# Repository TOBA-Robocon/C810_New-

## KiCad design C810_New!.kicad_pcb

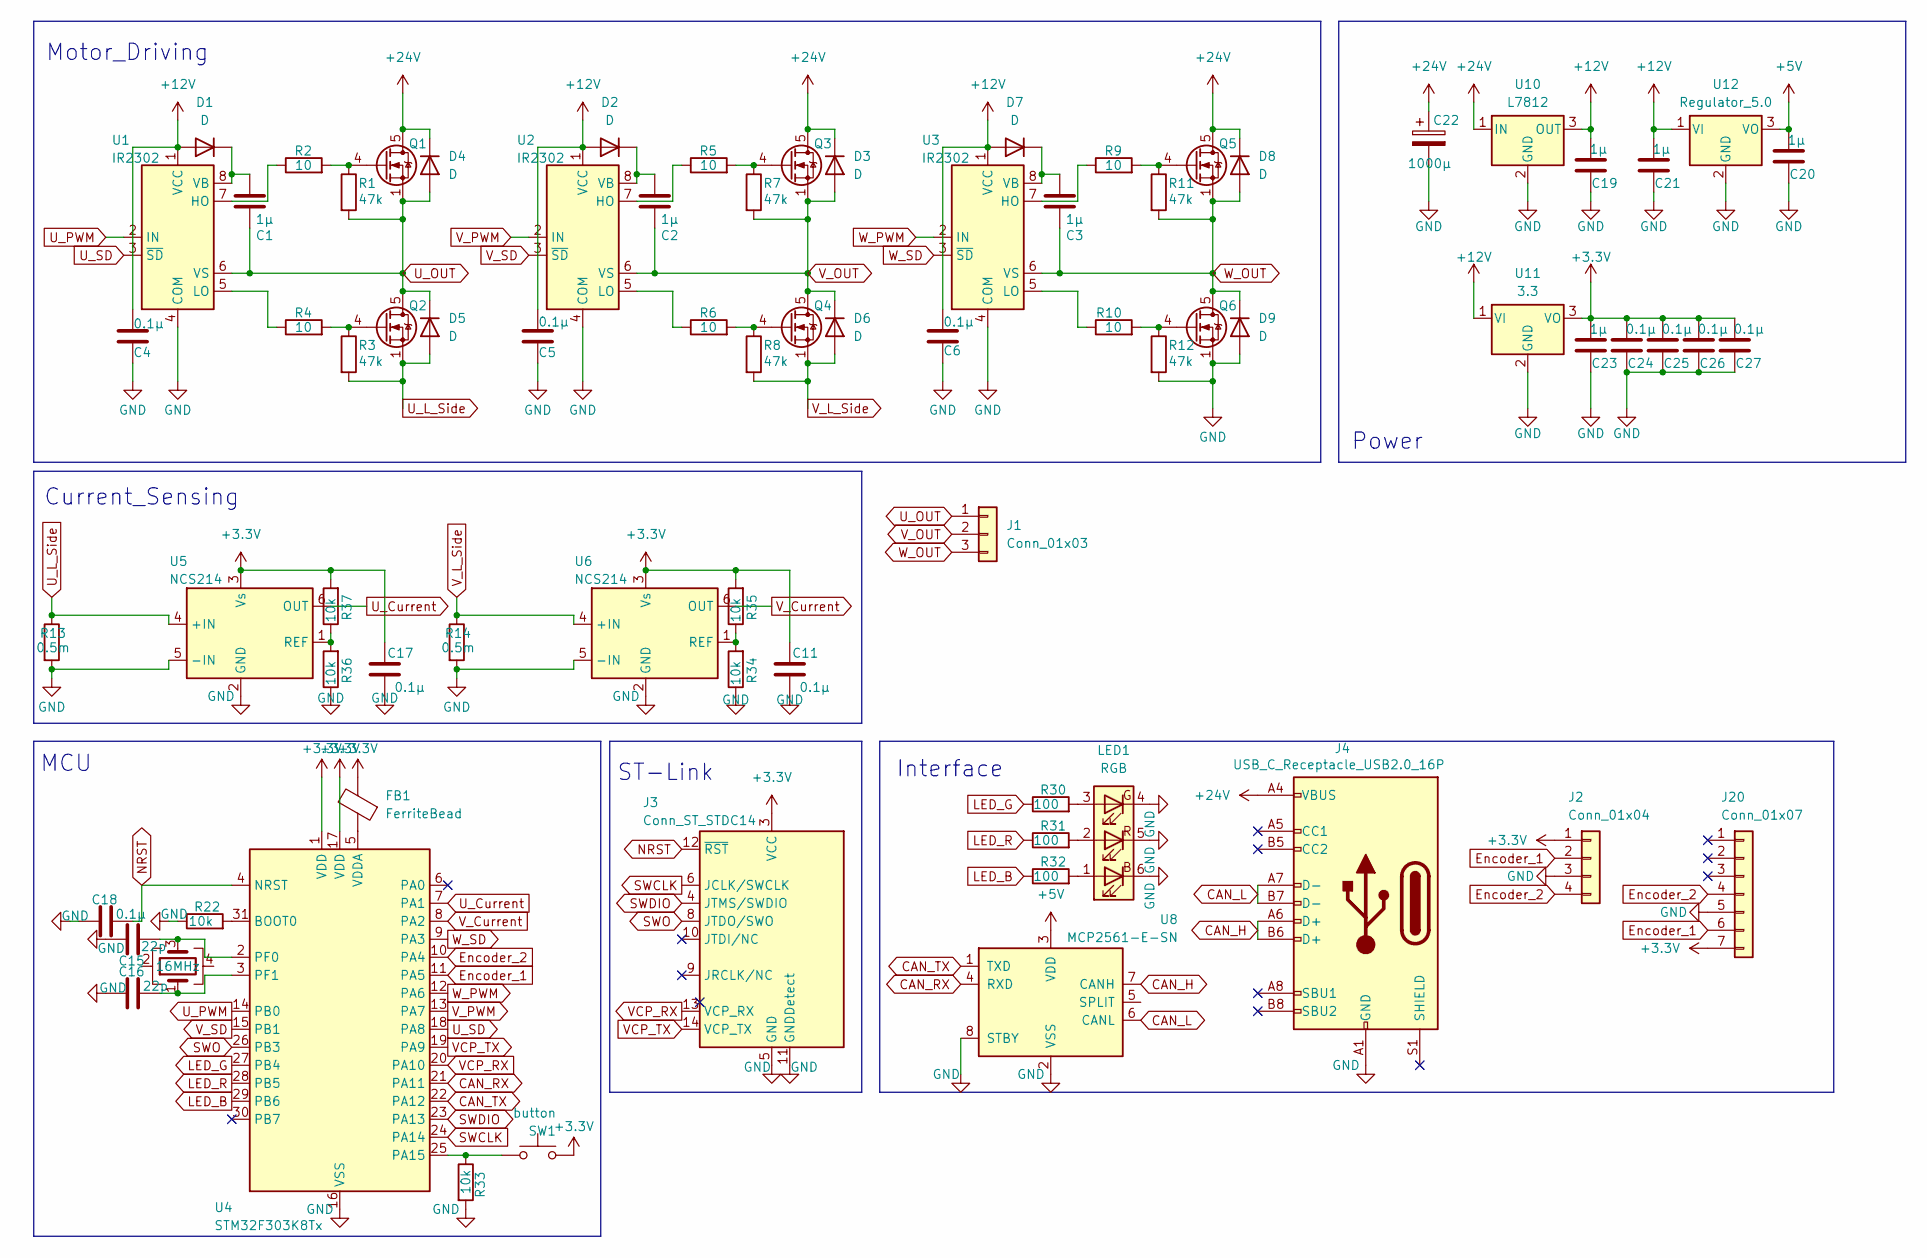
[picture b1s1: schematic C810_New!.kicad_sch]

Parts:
C1, C2, C3, C19, C20, C21, C23: 1μ; C_0603_1608Metric
C4, C5, C6, C11, C17, C18, C24, C25, C26, C27: 0.1μ; C_0603_1608Metric
C15, C16: 22p; C_0603_1608Metric
C22: 1000μ; CP_Elec_6.3x7.7
D1, D2, D3, D4, D5, D6, D7, D8, D9: D; D_SOD-123F
FB1: FerriteBead; L_0805_2012Metric_Pad1.05x1.20mm_HandSolder
J1: Conn_01x03; MR30
J2: Conn_01x04; JST_GH_SM04B-GHS-TB_1x04-1MP_P1.25mm_Horizontal
J3: Conn_ST_STDC14; PinHeader_2x07_P1.27mm_Vertical
J4: USB_C_Receptacle_USB2.0_16P; USB_C_Receptacle_GCT_USB4085
J20: Conn_01x07; JST_GH_SM07B-GHS-TB_1x07-1MP_P1.25mm_Horizontal
LED1: RGB; LED_ROHM_SMLVN6
Q1, Q2, Q3, Q4, Q5, Q6: BSC159N10LSFG; TDSON-8-1
R1, R3, R7, R8, R11, R12: 47k; R_0603_1608Metric
R2, R4, R5, R6, R9, R10: 10; R_0603_1608Metric
R13, R14: 0.5m; R_2512_6332Metric
R22, R33, R34, R35, R36, R37: 10k; R_0603_1608Metric
R30, R31, R32: 100; R_0603_1608Metric
SW1: button; SW_Push_1P1T_NO_Vertical_Wuerth_434133025816
U1, U2, U3: IR2302; SOIC-8_3.9x4.9mm_P1.27mm
U4: STM32F303K8Tx; LQFP-32_7x7mm_P0.8mm
U5, U6: NCS214; SOT-363_SC-70-6_Handsoldering
U8: MCP2561-E-SN; SOIC-8_3.9x4.9mm_P1.27mm
U10: L7812; TO-252-2
U11: 3.3; TO-252-2
U12: Regulator_5.0; TO-252-2
Y2: 16MHz; Crystal_SMD_3225-4Pin_3.2x2.5mm

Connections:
+3.3V: C11.1, C17.1, C23.1, C24.1, C25.1, C26.1, C27.1, FB1.2, J2.1, J3.3 (VCC), J20.7, R35.2, R37.2, SW1.2, U4.1 (VDD), U4.17 (VDD), U5.3 (Vs), U6.3 (Vs), U11.3 (VO)
+5V: C20.1, U8.3 (VDD), U12.3 (VO)
+12V: C4.1, C5.1, C6.1, C19.1, C21.1, D1.2 (A), D2.2 (A), D7.2 (A), U1.1 (VCC), U2.1 (VCC), U3.1 (VCC), U10.3 (OUT), U11.1 (VI), U12.1 (VI)
+24V: C22.1, D3.1 (K), D4.1 (K), D8.1 (K), J4.A4 (VBUS), J4.A9 (VBUS), J4.B4 (VBUS), J4.B9 (VBUS), Q1.5 (D), Q3.5 (D), Q5.5 (D), U10.1 (IN)
CAN_H: J4.A6 (D+), J4.B6 (D+), U8.7 (CANH)
CAN_L: J4.A7 (D-), J4.B7 (D-), U8.6 (CANL)
CAN_RX: U4.21 (PA11), U8.4 (RXD)
CAN_TX: U4.22 (PA12), U8.1 (TXD)
Encoder_1: J2.2, J20.6, U4.11 (PA5)
Encoder_2: J2.4, J20.4, U4.10 (PA4)
GND: C4.2, C5.2, C6.2, C11.2, C15.1, C16.1, C17.2, C18.1, C19.2, C20.2, C21.2, C22.2, C23.2, C24.2, C25.2, C26.2, C27.2, D9.2 (A), J2.3, J3.5 (GND), J3.7 (GND), J3.11 (GNDDetect), J4.A1 (GND), J4.A12 (GND), J4.B1 (GND), J4.B12 (GND), J20.5, LED1.4 (GK), LED1.5 (RK), LED1.6 (BK), Q6.1 (S), Q6.2 (S), Q6.3 (S), R12.2, R13.2, R14.2, R22.1, R33.2, R34.1, R36.1, U1.4 (COM), U2.4 (COM), U3.4 (COM), U4.16 (VSS), U4.32 (VSS), U5.2 (GND), U5.5 (-IN), U6.2 (GND), U6.5 (-IN), U8.2 (VSS), U8.8 (STBY), U10.2 (GND), U11.2 (GND), U12.2 (GND)
LED_B: R32.1, U4.29 (PB6)
LED_G: R30.1, U4.27 (PB4)
LED_R: R31.1, U4.28 (PB5)
NRST: C18.2, J3.12 (~RST), U4.4 (NRST)
unnamed: C1.1, D1.1 (K), U1.8 (VB)
unnamed: C2.1, D2.1 (K), U2.8 (VB)
unnamed: C3.1, D7.1 (K), U3.8 (VB)
unnamed: LED1.1 (BA), R32.2
unnamed: LED1.3 (GA), R30.2
unnamed: LED1.2 (RA), R31.2
unnamed: Q1.4 (G), R1.1, R2.2
unnamed: Q2.4 (G), R3.1, R4.2
unnamed: Q3.4 (G), R5.2, R7.1
unnamed: Q4.4 (G), R6.2, R8.1
unnamed: Q5.4 (G), R9.2, R11.1
unnamed: Q6.4 (G), R10.2, R12.1
unnamed: R2.1, U1.7 (HO)
unnamed: R4.1, U1.5 (LO)
unnamed: R5.1, U2.7 (HO)
unnamed: R6.1, U2.5 (LO)
unnamed: R9.1, U3.7 (HO)
unnamed: R10.1, U3.5 (LO)
unnamed: R22.2, U4.31 (BOOT0)
unnamed: R33.1, SW1.1, U4.25 (PA15)
unnamed: C15.2, U4.2 (PF0), Y2.3
unnamed: C16.2, U4.3 (PF1), Y2.1
unnamed: FB1.1, U4.5 (VDDA)
unnamed: R36.2, R37.1, U5.1 (REF)
unnamed: R34.2, R35.1, U6.1 (REF)
SWCLK: J3.6 (JCLK/SWCLK), U4.24 (PA14)
SWDIO: J3.4 (JTMS/SWDIO), U4.23 (PA13)
SWO: J3.8 (JTDO/SWO), U4.26 (PB3)
U_Current: U4.7 (PA1), U5.6 (OUT)
U_L_Side: D5.2 (A), Q2.1 (S), Q2.2 (S), Q2.3 (S), R3.2, R13.1, U5.4 (+IN)
U_OUT: C1.2, D4.2 (A), D5.1 (K), J1.1, Q1.1 (S), Q1.2 (S), Q1.3 (S), Q2.5 (D), R1.2, U1.6 (VS)
U_PWM: U1.2 (IN), U4.14 (PB0)
U_SD: U1.3 (~SD), U4.18 (PA8)
VCP_RX: J3.13 (VCP_RX), U4.20 (PA10)
VCP_TX: J3.14 (VCP_TX), U4.19 (PA9)
V_Current: U4.8 (PA2), U6.6 (OUT)
V_L_Side: D6.2 (A), Q4.1 (S), Q4.2 (S), Q4.3 (S), R8.2, R14.1, U6.4 (+IN)
V_OUT: C2.2, D3.2 (A), D6.1 (K), J1.2, Q3.1 (S), Q3.2 (S), Q3.3 (S), Q4.5 (D), R7.2, U2.6 (VS)
V_PWM: U2.2 (IN), U4.13 (PA7)
V_SD: U2.3 (~SD), U4.15 (PB1)
W_OUT: C3.2, D8.2 (A), D9.1 (K), J1.3, Q5.1 (S), Q5.2 (S), Q5.3 (S), Q6.5 (D), R11.2, U3.6 (VS)
W_PWM: U3.2 (IN), U4.12 (PA6)
W_SD: U3.3 (~SD), U4.9 (PA3)

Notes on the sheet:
Motor_Driving
ST-Link
Interface
Power
MCU
Current_Sensing

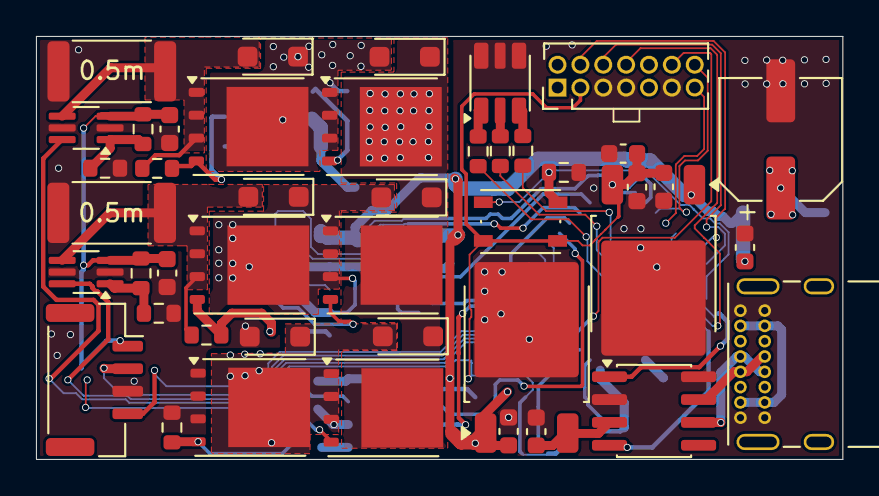
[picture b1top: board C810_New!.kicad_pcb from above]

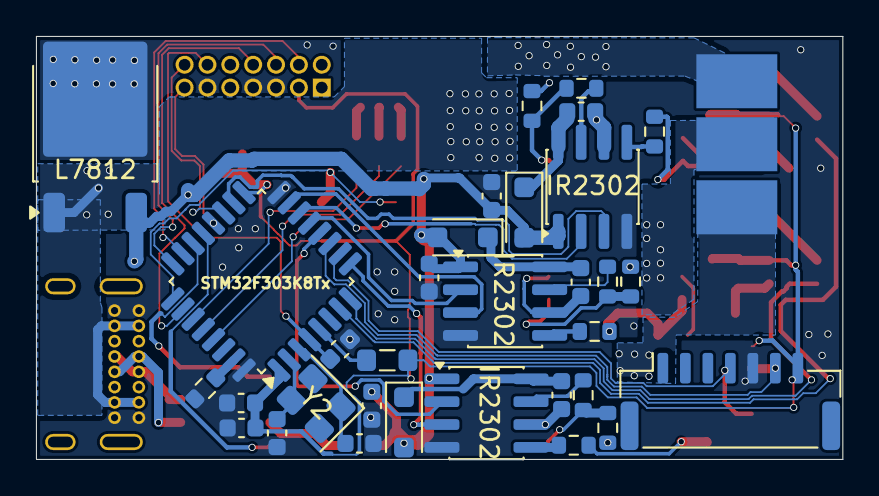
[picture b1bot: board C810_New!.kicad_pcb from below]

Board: 2 copper layers, 44.8 x 23.5 mm, 77 parts (33 on the bottom side), 58 nets.

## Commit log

2025-11-24 first_commit
2025-11-24 LowSideでの電流検出に変更
2025-11-24 M3508用のGHコネクタを追加
    PCBの配線し直し開始
2025-11-24 配線全削除
2025-11-25 C610と同じサイズは無理すぎ
2025-12-01 あたおかレイアウトを考えてる
2025-12-01 配線が無理すぎるので寝る
2025-12-02 gomimimimi
2025-12-02 配線完了
